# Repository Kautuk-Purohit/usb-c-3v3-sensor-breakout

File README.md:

# KiCad PCB Project

A fabrication ready PCB designed as a portfolio project.  
Includes a full schematic and PCB layout, verified with ERC (Electrical Rules Check) and DRC (Design Rules Check), and validated Gerbers and drills in Gerber Viewer.

---

## Table of Contents
- [Overview](#overview)
- [Key Features](#key-features)
- [Project Status](#project-status)
- [Repo Structure](#repo-structure)
- [Verification](#verification)
- [Manufacturing Outputs](#manufacturing-outputs)
- [How to Open](#how-to-open)
- [Key Images](#images)
- [Next Improvements](#next-improvements)

---

## Overview
This project demonstrates an end to end PCB workflow:

schematic design → layout and routing → design rule checks → manufacturing outputs

The goal is to show practical board design skills (power, interfaces, layout, manufacturability) 

---

## Key Features
- USB power input with on board 3.3V regulation
- Microcontroller based system design
- I2C (Inter Integrated Circuit) sensor bus (IMU)
- Labeled connectors and test points for bring up
- Ground plane implemented
- Manufacturing package generated (Gerbers + PTH and NPTH drills)
- BOM and pick and place exported for assembly readiness

---

## Project Status
- [x] Placement and routing complete
- [x] Ground plane set
- [x] ERC clean
- [x] DRC clean
- [x] 3D view checked for footprint consistency
- [x] Gerbers generated
- [x] Drill files generated (PTH + NPTH)
- [x] Gerbers and drills verified in Gerber Viewer
- [X] BOM committed
- [X] Pick and place committed

---

## Repo Structure
```text
.
├── kicad/                     # KiCad schematic + PCB
├── manufacturing/
│   ├── gerbers/               # plotted Gerbers
│   ├── drill/                 # Excellon drills (PTH + NPTH)
│   ├── bom/                   # BOM exports
│   ├── assembly/              # pick and place / position outputs
│   └── release/               # upload ready ZIP(s)
└── images/                    
│   ├── manufacturing/         # Manufacturing related pictures
│   ├── pcb_design/            # PCB Design pictures
│   ├── schematic/             # Schematic related pictures
```
---

## Verification
- ERC (Electrical Rules Check): clean
- DRC (Design Rules Check): clean
- 3D Viewer: checked for footprint consistency
- Gerber Viewer: verified copper, mask, silkscreen, outline, and drill alignment (PTH + NPTH)

---

## Manufacturing Outputs
### Fabrication package (upload ready)
[RELEASE FILE](manufacturing/release/PCB_RELEASE_GERBER_DRILL.zip)

### Assembly data
- [BOM](manufacturing/bom/usb_c_sensor_breakout.csv)
- [Pick and Place POS Files](manufacturing/assembly)

---

## How to Open
1. Install KiCad (project created in KiCad 9.0).
2. Open the project in `kicad/`.
3. Review:
   - Schematic (`.kicad_sch`)
   - PCB layout (`.kicad_pcb`)
   - 3D Viewer
4. Manufacturing outputs are in `manufacturing/`.

---

## Images

### PCB 3D front:

### PCB 3D back:

### PCB Final Layout: 

### Gerber overlay: 

### Drill overlay (PTH + NPTH): 

---

## Next Improvements
In a future revision:
- Add fiducials
- Add additional ESD protection (eg. for external connectors)
- Improve silkscreen placement and reference readability
- Adding NPTH drills (mounting holes) for realistic usage

---

## License
All Rights Reserved.

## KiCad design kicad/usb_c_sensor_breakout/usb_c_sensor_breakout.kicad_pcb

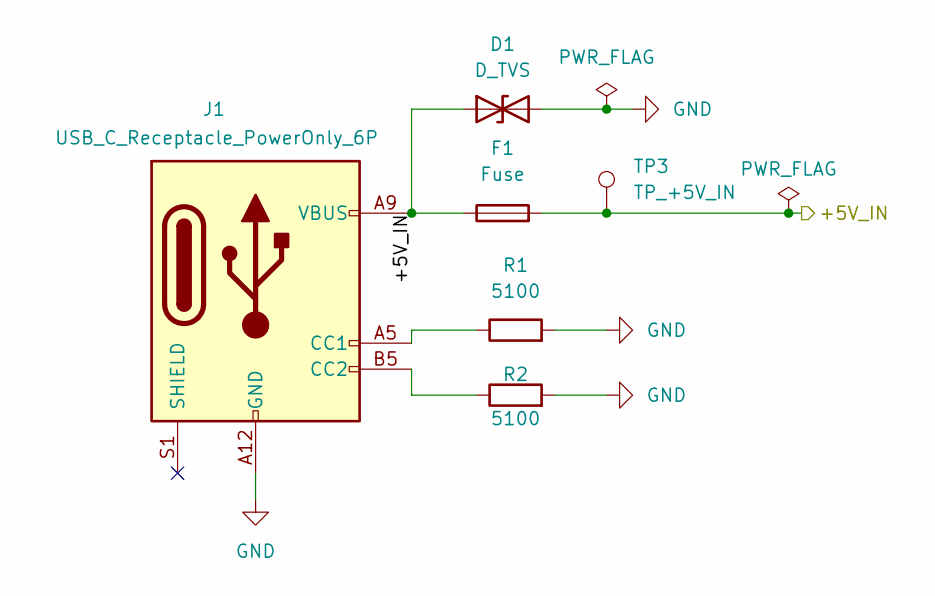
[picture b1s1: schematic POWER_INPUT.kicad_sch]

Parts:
D1: D_TVS; D_SOD-123
F1: Fuse; Fuse_1812_4532Metric
J1: USB_C_Receptacle_PowerOnly_6P; USB_C_Receptacle_HRO_TYPE-C-31-M-17
R1, R2: 5100; R_0603_1608Metric
TP3: TP_+5V_IN; TestPoint_Pad_D1.5mm

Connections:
/POWER_INPUT/+5V_IN: D1.1 (A1), F1.1, F1.2, J1.A9 (VBUS), J1.B9 (VBUS), TP3.1; also elsewhere on the board
GND: D1.2 (A2), J1.A12 (GND), J1.B12 (GND), R1.2, R2.2; also elsewhere on the board
unnamed: J1.A5 (CC1), R1.1
unnamed: J1.B5 (CC2), R2.1

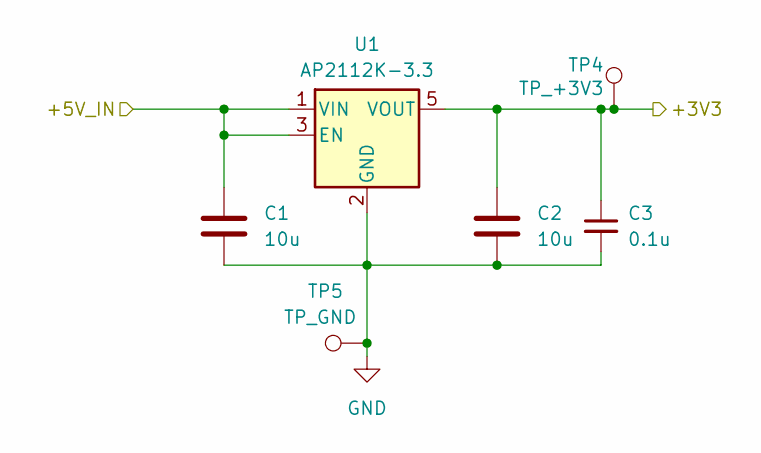
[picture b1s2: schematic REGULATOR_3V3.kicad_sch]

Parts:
C1, C2: 10u; C_0603_1608Metric
C3: 0.1u; C_0603_1608Metric
TP4: TP_+3V3; TestPoint_Pad_D1.5mm
TP5: TP_GND; TestPoint_Pad_D1.5mm
U1: AP2112K-3.3; SOT-23-5

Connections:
/+3V3: C2.2, C3.1, TP4.1, U1.5 (VOUT); also elsewhere on the board
/POWER_INPUT/+5V_IN: C1.2, U1.1 (VIN), U1.3 (EN); also elsewhere on the board
GND: C1.1, C2.1, C3.2, TP5.1, U1.2 (GND); also elsewhere on the board

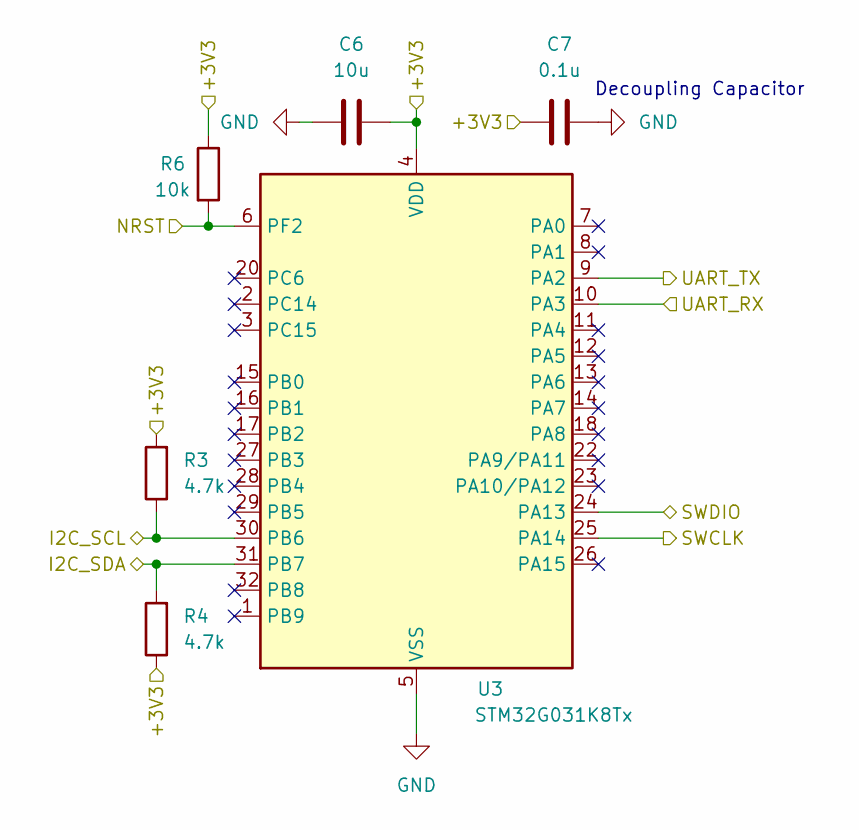
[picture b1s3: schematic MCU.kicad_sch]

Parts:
C6: 10u; C_0603_1608Metric
C7: 0.1u; C_0603_1608Metric
R3, R4: 4.7k; R_0603_1608Metric
R6: 10k; R_0603_1608Metric
U3: STM32G031K8Tx; LQFP-32_7x7mm_P0.8mm

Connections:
/+3V3: C6.2, C7.1, R3.2, R4.1, R6.1, U3.4 (VDD); also elsewhere on the board
/CONNECTORS/I2C_SCL: R3.1, U3.30 (PB6); also elsewhere on the board
/CONNECTORS/I2C_SDA: R4.2, U3.31 (PB7); also elsewhere on the board
/CONNECTORS/NRST: R6.2, U3.6 (PF2); also elsewhere on the board
/CONNECTORS/SWCLK: U3.25 (PA14); also elsewhere on the board
/CONNECTORS/SWDIO: U3.24 (PA13); also elsewhere on the board
/CONNECTORS/UART_RX: U3.10 (PA3); also elsewhere on the board
/CONNECTORS/UART_TX: U3.9 (PA2); also elsewhere on the board
GND: C6.1, C7.2, U3.5 (VSS); also elsewhere on the board

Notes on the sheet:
Decoupling Capacitor

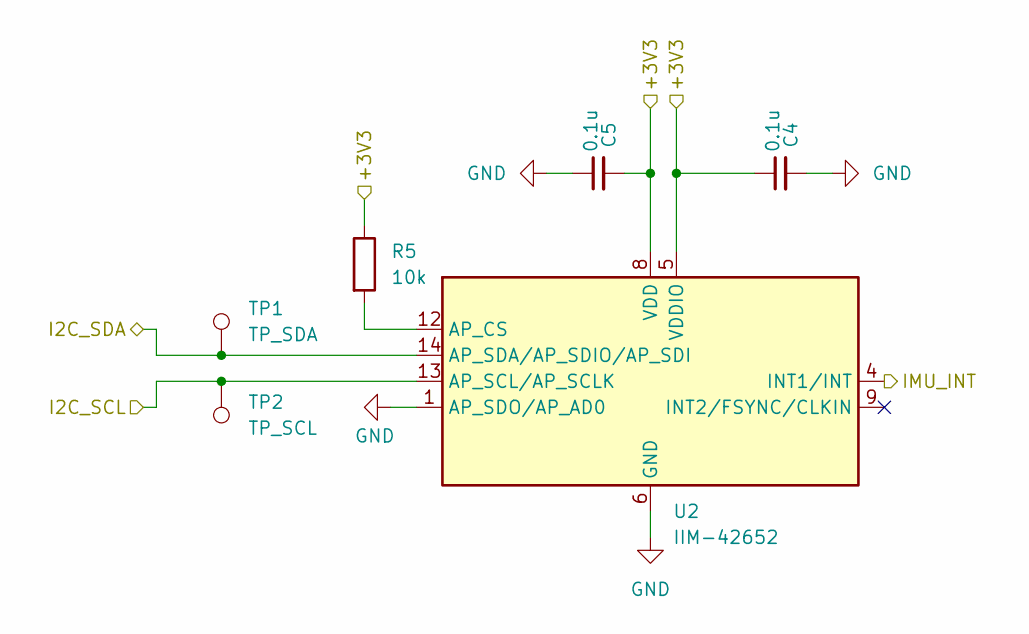
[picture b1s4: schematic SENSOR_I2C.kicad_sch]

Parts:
C4, C5: 0.1u; C_0603_1608Metric
R5: 10k; R_0603_1608Metric
TP1: TP_SDA; TestPoint_Pad_D1.5mm
TP2: TP_SCL; TestPoint_Pad_D1.5mm
U2: IIM-42652; Bosch_LGA-14_3x2.5mm_P0.5mm

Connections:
/+3V3: C4.1, C5.2, R5.1, U2.5 (VDDIO), U2.8 (VDD); also elsewhere on the board
/CONNECTORS/I2C_SCL: TP2.1, U2.13 (AP_SCL/AP_SCLK); also elsewhere on the board
/CONNECTORS/I2C_SDA: TP1.1, U2.14 (AP_SDA/AP_SDIO/AP_SDI); also elsewhere on the board
/SENSOR_I2C/IMU_INT: U2.4 (INT1/INT)
GND: C4.2, C5.1, U2.1 (AP_SDO/AP_AD0), U2.6 (GND), U2.7 (GND); also elsewhere on the board
unnamed: R5.2, U2.12 (AP_CS)

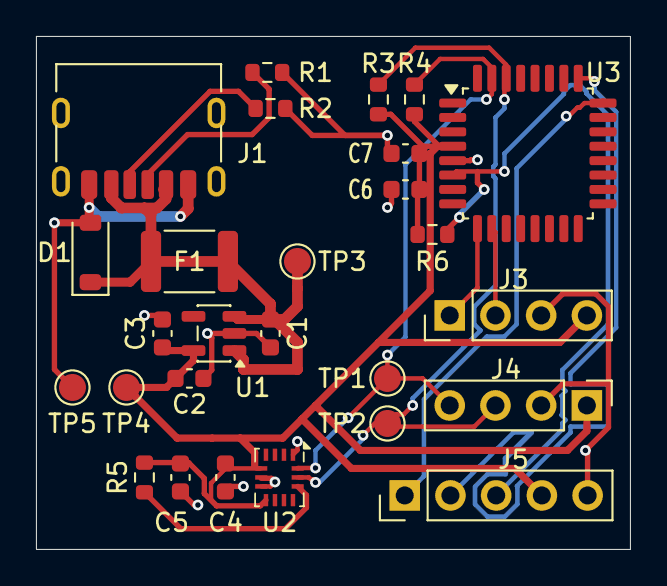
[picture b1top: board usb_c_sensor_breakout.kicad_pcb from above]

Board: 2 copper layers, 33.0 x 28.5 mm, 27 parts (0 on the bottom side), 13 nets.

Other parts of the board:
J3: J_UART; PinHeader_1x04_P2.54mm_Vertical
J4: J_I2C_EXP; PinHeader_1x04_P2.54mm_Vertical
J5: J_SWD; PinHeader_1x05_P2.54mm_Vertical

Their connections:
/+3V3: J3.4, J4.1, J5.4; also elsewhere on the board
/CONNECTORS/I2C_SCL: J4.3; also elsewhere on the board
/CONNECTORS/I2C_SDA: J4.4; also elsewhere on the board
/CONNECTORS/NRST: J5.3; also elsewhere on the board
/CONNECTORS/SWCLK: J5.2; also elsewhere on the board
/CONNECTORS/SWDIO: J5.1; also elsewhere on the board
/CONNECTORS/UART_RX: J3.2; also elsewhere on the board
/CONNECTORS/UART_TX: J3.1; also elsewhere on the board
GND: J3.3, J4.2, J5.5; also elsewhere on the board

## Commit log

2026-02-05 Day 0: project structure and KiCad project
2026-02-05 Fix: rename README/gitignore/notes
2026-02-14 commit2: usbc + regulator + i2c pullups + sensor header + testpoint
2026-02-15 Commit3: Regulators + Top-level + I2C sensor upgrade
2026-02-15 Commit 4: Updated annotation + footprints
2026-02-15 Commit 5: MCU + Final Schematic Touches + Labelling + USBc fix
2026-02-20 Commit 6: Finished PCB + Updated Schematic
2026-02-20 Commit 7: Fab outputs (Gerbers + Drills) - Verified in Gerber Viewer
2026-02-20 Commit 8: BOM + pick-and-place outputs
2026-02-20 Commit 9: Added Screenshots
2026-02-20 Commit 10: File Cleanup
